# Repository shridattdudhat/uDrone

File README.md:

# μDrone

***Documentation yet to be updated!***

Email on [**electroShri@gmail.com**](mailto:electroShri@gmail.com) to buy DIY kit. That will help in development of this project.

## Contributing
Pull requests are welcome. For major changes, please open an issue first to discuss what you would like to change.

Please make sure to update tests as appropriate.

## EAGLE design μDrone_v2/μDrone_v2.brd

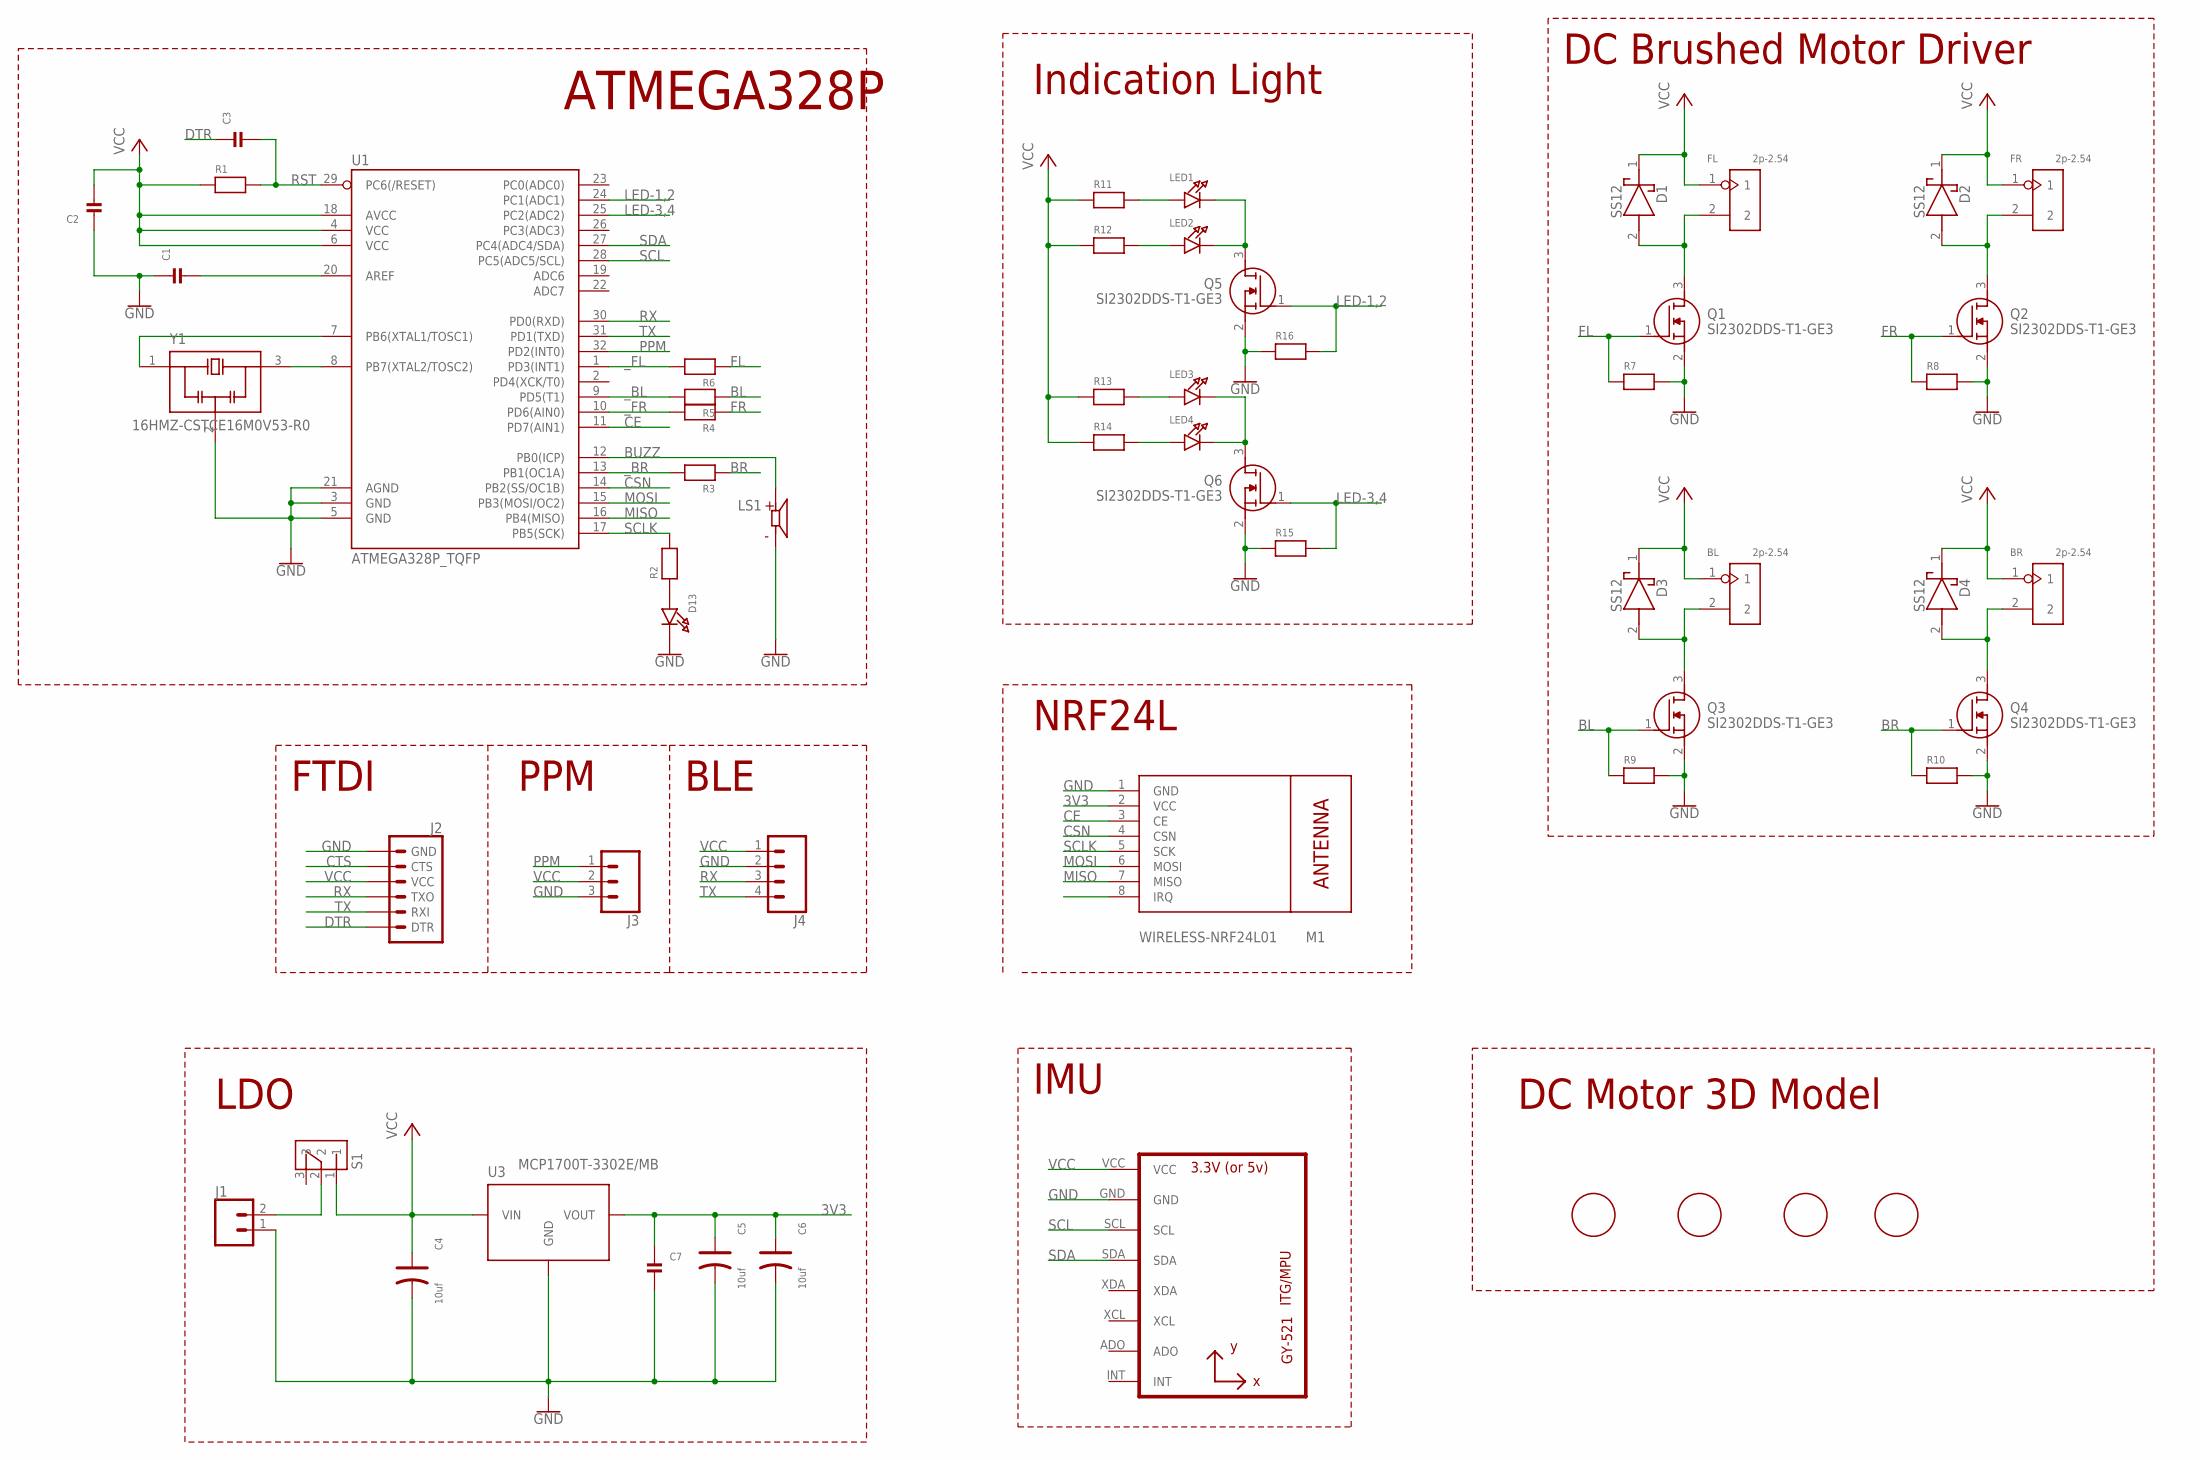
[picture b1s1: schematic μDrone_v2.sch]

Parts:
BL: 2p-2.54; H2-2.54-F
BR: 2p-2.54; H2-2.54-F
C1, C2, C3, C7: CAP_CERAMIC0805; C0805
C4, C5, C6: 10uf; AVX-A
D1, D2, D3, D4: SS12; DIOM5227X250N
D13: LED0805_NOOUTLINE; CHIPLED_0805_NOOUTLINE
FL: 2p-2.54; H2-2.54-F
FR: 2p-2.54; H2-2.54-F
J1: CONN_02-JST-2-PTH-NO_SILK; JST-2-PTH-NS
J2: 6_PIN_SERIAL_TARGETSILK; 6_PIN_SERIAL_TARGET_SIDE_W_SILK
J3: CONN_03; 1X03
J4: CONN_04; 1X04
LED1, LED2, LED3, LED4: LED0805; CHIPLED_0805
LS1: CMI-9655S-SMT; CUI_CMI-9655S-SMT
M1: WIRELESS-NRF24L01
Q1, Q2, Q3, Q4, Q5, Q6: SI2302DDS-T1-GE3; SOT95P237X112-3N
R1, R2, R3, R4, R5, R6, R7, R8, R9, R10, R11, R12, R13, R14, R15, R16: RESISTOR0805; R0805
S1: OS102011MS2QN1; SW_OS102011MS2QN1
U1: ATMEGA328P_TQFP; TQFP32-08
U2: GY-521MPU6050; GY-521
U3: MCP1700T-3302E/MB
U$1, U$2, U$3, U$4: MICRO-DC-MOTOR-WITH-PROP; MICRO-DC
Y1: 16HMZ-CSTCE16M0V53-R0; OSC_CSTCE16M0V53-R0

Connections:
3V3: C5.+, C6.+, C7.1, M1.2 (VCC), U3.3 (VOUT)
BL: Q3.1 (G), R5.1, R9.1
BR: Q4.1 (G), R3.1, R10.1
BUZZ: LS1.P, U1.12 (PB0(ICP))
CE: M1.3 (CE), U1.11 (PD7(AIN1))
CSN: M1.4 (CSN), U1.14 (PB2(SS/OC1B))
CTS: J2.P$5 (CTS)
DTR: C3.1, J2.P$1 (DTR)
FL: Q1.1 (G), R6.1, R7.1
FR: Q2.1 (G), R4.1, R8.1
GND: C1.1, C2.1, C4.-, C5.-, C6.-, C7.2, D13.C, J1.1, J2.P$6 (GND), J3.3, J4.2, LS1.N, M1.1 (GND), Q1.2 (S), Q2.2 (S), Q3.2 (S), Q4.2 (S), Q5.2 (S), Q6.2 (S), R7.2, R8.2, R9.2, R10.2, R15.1, R16.1, U1.3 (GND), U1.5 (GND), U1.21 (AGND), U2.GND, U3.1 (GND), Y1.2 (GND)
IRQ: M1.8 (IRQ)
LED-1,2: Q5.1 (G), R16.2, U1.24 (PC1(ADC1))
LED-3,4: Q6.1 (G), R15.2, U1.25 (PC2(ADC2))
MISO: M1.7 (MISO), U1.16 (PB4(MISO))
MOSI: M1.6 (MOSI), U1.15 (PB3(MOSI/OC2))
unnamed: U1.8 (PB7(XTAL2/TOSC2)), Y1.3 (OUT)
unnamed: D13.A, R2.1
unnamed: C1.2, U1.20 (AREF)
unnamed: U1.7 (PB6(XTAL1/TOSC1)), Y1.1 (IN)
unnamed: D2.2 (A), FR.2, Q2.3 (D)
unnamed: D1.2 (A), FL.2, Q1.3 (D)
unnamed: BL.2, D3.2 (A), Q3.3 (D)
unnamed: BR.2, D4.2 (A), Q4.3 (D)
unnamed: LED1.A, R11.2
unnamed: LED2.A, R12.2
unnamed: LED3.A, R13.2
unnamed: LED4.A, R14.2
unnamed: LED1.C, LED2.C, Q5.3 (D)
unnamed: J1.2, S1.2
unnamed: LED3.C, LED4.C, Q6.3 (D)
PPM: J3.1, U1.32 (PD2(INT0))
RST: C3.2, R1.2, U1.29 (PC6(/RESET))
RX: J2.P$2 (TXO), J4.3, U1.30 (PD0(RXD))
SCL: U1.28 (PC5(ADC5/SCL)), U2.SCL
SCLK: M1.5 (SCK), R2.2, U1.17 (PB5(SCK))
SDA: U1.27 (PC4(ADC4/SDA)), U2.SDA
TX: J2.P$3 (RXI), J4.4, U1.31 (PD1(TXD))
VCC: BL.1, BR.1, C2.2, C4.+, D1.1 (K), D2.1 (K), D3.1 (K), D4.1 (K), FL.1, FR.1, J2.P$4 (VCC), J3.2, J4.1, R1.1, R11.1, R12.1, R13.1, R14.1, S1.1, U1.4 (VCC), U1.6 (VCC), U1.18 (AVCC), U2.VCC, U3.2 (VIN), U3.2.1 (VIN)
_BL: R5.2, U1.9 (PD5(T1))
_BR: R3.2, U1.13 (PB1(OC1A))
_FL: R6.2, U1.1 (PD3(INT1))
_FR: R4.2, U1.10 (PD6(AIN0))

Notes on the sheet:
ATMEGA328P
Indication Light
DC Brushed Motor Driver
DC Motor 3D Model
IMU
NRF24L
BLE
PPM
FTDI
LDO

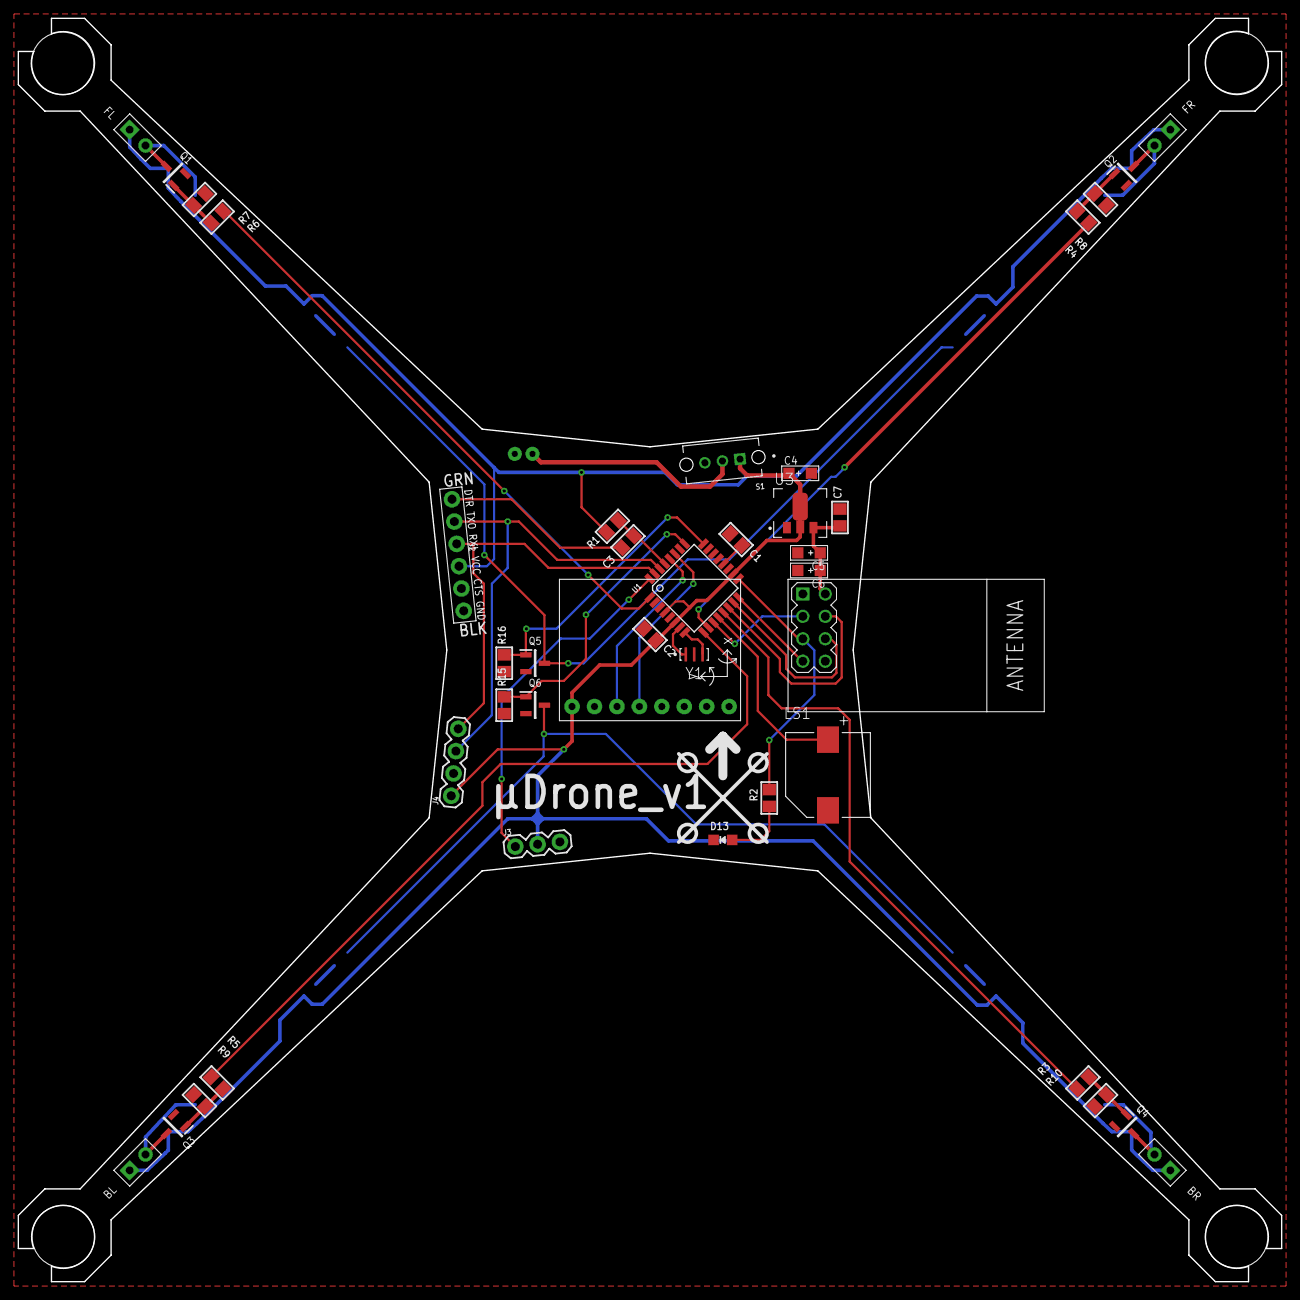
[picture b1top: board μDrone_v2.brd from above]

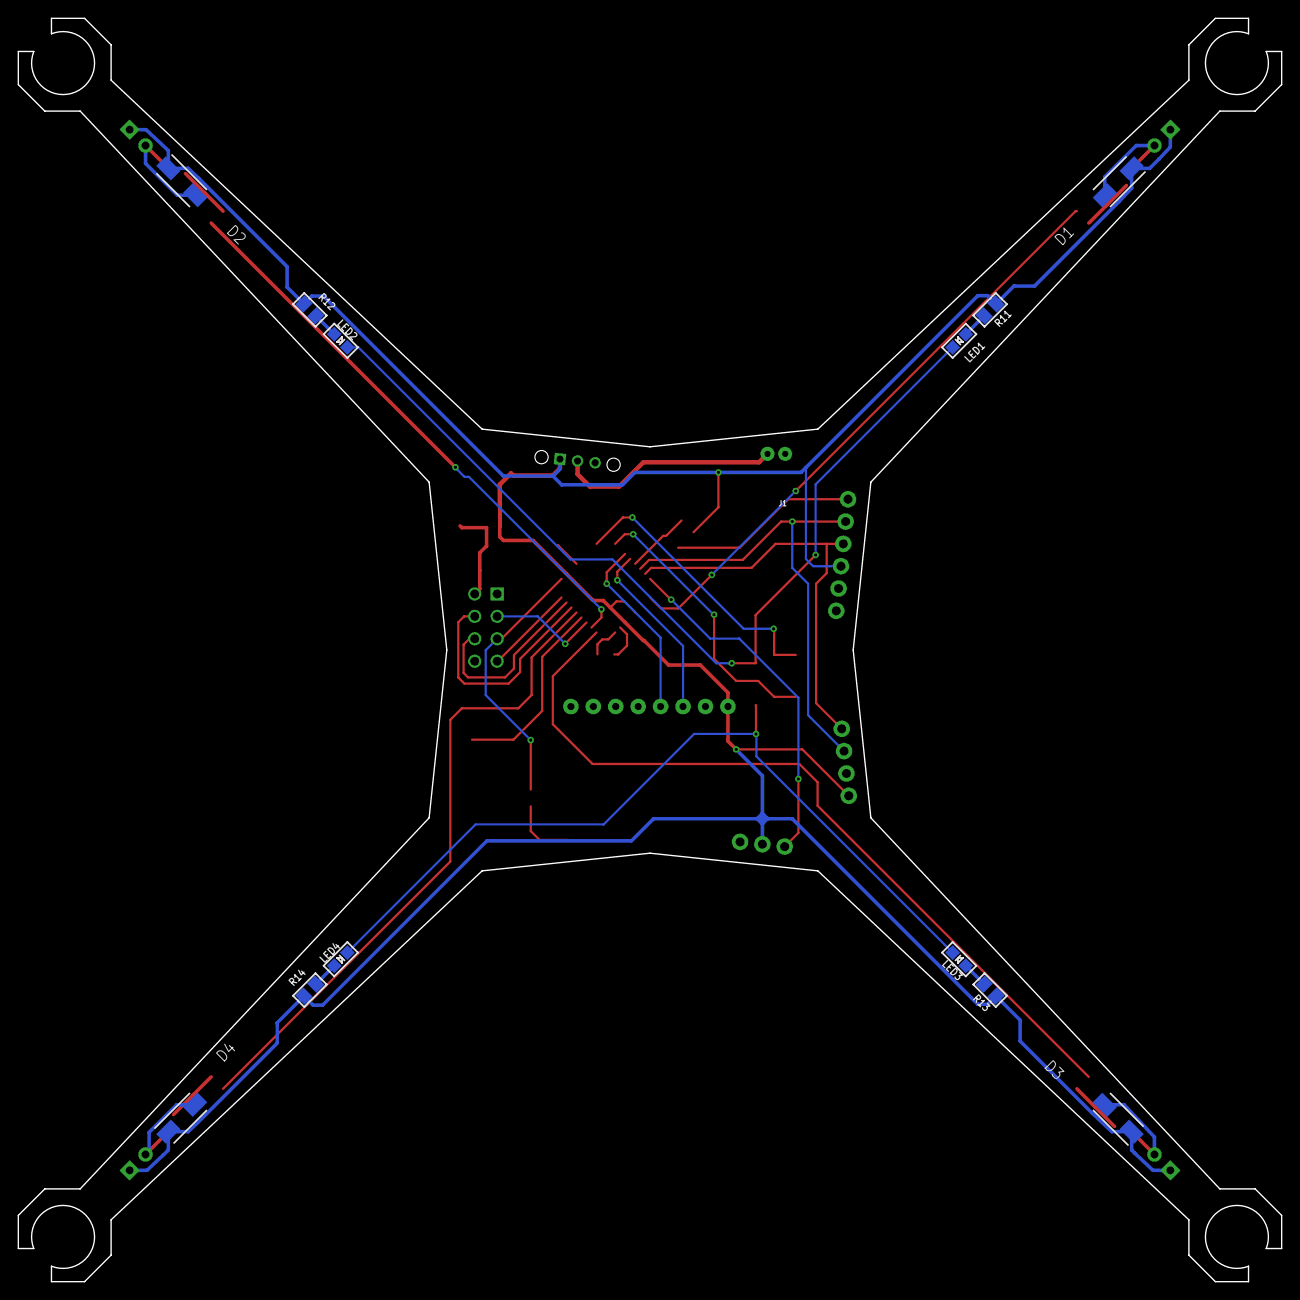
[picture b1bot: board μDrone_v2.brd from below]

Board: 2 copper layers, 143.0 x 143.0 mm, 57 parts (13 on the bottom side), 41 nets.

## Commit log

2020-06-10 move μDrone_v1 from projects to github
2020-06-14 gerber file generation
2020-06-14 Set theme jekyll-theme-cayman
2020-06-14 image upload
2020-06-14 Set theme jekyll-theme-slate
2020-07-17 MultiWii
2020-10-31 issue with MultiWii
2021-07-27 Create LICENSE
2021-07-28 with bluepill stm32

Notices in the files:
parts and their libraries:
SparkFun-IC-Microcontroller: Licensing: Creative Commons ShareAlike 4.0 International - https://creativecommons.org/licenses/by-sa/4.0
